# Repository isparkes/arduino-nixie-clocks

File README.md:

# ArdunixNix6 / ArdunixNix4 Version 2
Code for a 6-digit / 4-digit Nixie Clock based on Arduino with NeoPixel backlights

This is the main code for an Arduino based Nixie clock, intended for the following clocks:
- [ModularRev3](https://www.nixieclock.biz/StoreModular.html)
- [Classic Rev6](https://www.nixieclock.biz/StoreClassicRev6.html)

The firmware now also covers the older V1 clocks with RAGB LED backlights -
Classic Rev4 / Rev5, All-In-One IN-14 and the Arduino All-In-One shield - which
used to live in
[NixieClockFirmwareV1](https://bitbucket.org/isparkes/nixiefirmwarev1). Both
the 6 digit and the 4 digit firmware build for either generation; pick the
board with a single define at build time, see [Building](#building) below.

Version 356 converges the code bases for Classic Rev6 and Modular Rev 3.01. If you have a Modular Rev3, please see previous versions!

This repository now holds both the firmware and the KiCad hardware designs.
Firmware lives under `Software/` and is built with PlatformIO rather than the
Arduino IDE; the board designs live under `Hardware/`. The ESP8266 time
provider and the five hardware repositories were each developed separately
for a while and have been merged back in with their histories intact. Both
clock generations are covered, and which firmware a board takes follows
directly from its generation: **the Classic Rev6 and the Modular Rev 3 run
the V2 firmware; every other design here runs the V1 firmware.** See
[Which firmware runs on which board](#which-firmware-runs-on-which-board).

#### Features:
- Open source (CC BY-NC 4.0, see [LICENSE](LICENSE))
- Wifi Interface for an ESP8266 (included, see `Software/src/WifiTimeProviderESP8266/`)
- Real Time Clock interface for DS3231
- Digit fading with configurable fade length
- Digit scrollback with configurable scroll speed
- Configuration stored in EEPROM
- Low hardware component count (as much as possible done in code)
- Single button operation with software debounce
- Single K155ID1 for digit display (other versions use 2 or even 6!)
- Highly modular code
- RGB Back lighting
- Automatic linear dimming using light sensor

#### Building

The software is a [PlatformIO](https://platformio.org/) project. Install
PlatformIO Core (or the VSCode extension), then from the `Software/` directory:

```
pio run                                 # build everything
pio run -e nixie6digit                  # build the 6 digit clock firmware
pio run -e nixie4digit -t upload        # build and flash the 4 digit firmware
pio run -e wifitimeprovider -t upload   # build and flash the ESP8266 module
pio run -t clean                        # remove build products
pio device monitor                      # serial monitor
```

Pick the environment that matches your clock:

| Environment | Clock | Backlight | Source |
| --- | --- | --- | --- |
| `nixie6digit` | Classic Rev6, Modular Rev 3.01 | NeoPixel | `src/Firmware6Digit/` |
| `nixie6digitV1` | Classic Rev4 / Rev5, All-In-One IN-14, Arduino AIO shield | RAGB | `src/Firmware6Digit/` |
| `nixie6digitV1aio` | All-In-One Rev1 (mixed up tube wiring) | RAGB | `src/Firmware6Digit/` |
| `nixie4digit` | 4 digit V2 clocks | NeoPixel | `src/Firmware4Digit/` |
| `nixie4digitV1` | 4 digit V1 clocks | RAGB | `src/Firmware4Digit/` |
| `wifitimeprovider` | ESP8266 (ESP-01 / ESP-01S) time provider | - | `src/WifiTimeProviderESP8266/` |

Each source tree covers both clock generations. The environments that share a
tree differ only in the one define each passes - `FWV2`, `FWV1` or
`FWV1_AIO_REV1` - which is the only hardware switch in the code. Everything
else, the pin map, the backlight driver and whether the PIR and decimal point
menus exist, is derived from it. The variant is set in
`Software/platformio.ini` and nowhere else; see the "Hardware variant
selection" block at the top of each `main.cpp` for what the defines select.
There is no `FWV1_AIO_REV1` for the 4 digit tree, because the All-In-One Rev1
is a 6 digit clock.

The 4 and 6 digit trees are still separate. Their display layouts differ in
function signatures and menu structure, not just in pin maps, so folding them
together would need a refactor rather than another define.

The V1 builds report the same I2C protocol as the V2 builds, so they need a
current ESP8266 time provider. Its settings page will offer PIR and decimal
point options that a V1 clock does not have; they are simply ignored.

The clock firmwares assume a bare ATmega328P at 16 MHz / 5 V, as fitted to
the Classic Rev6 and Modular Rev 3.01 boards, flashed through the FTDI header.
If you are building on stock Arduino hardware, change `board` and
`upload_speed` in `Software/platformio.ini` - the alternatives for Uno and Nano
are listed in the comments there.

All libraries are pulled by PlatformIO rather than committed here, so the
first build of each target needs a network connection. Every version is
pinned in `Software/platformio.ini`; please rebuild and check the reported
flash use before floating any of them.

| Library | Version | Used by |
| --- | --- | --- |
| `paulstoffregen/Time` | 1.5 | all targets |
| `northernwidget/DS3231` | 1.1.2 | the clock firmwares |
| `adafruit/Adafruit NeoPixel` | 1.1.3 | the clock firmwares, except the V1 builds |
| `bblanchon/ArduinoJson` | 5.13.2 (git tag) | `wifitimeprovider` |
| `tzapu/WiFiManager` | 0.15.0 (git tag) | `wifitimeprovider` |
| `me-no-dev/ESPAsyncUDP` | master, pinned by commit | `wifitimeprovider` |

ArduinoJson 5 and WiFiManager 0.15.0 come from upstream git tags because the
PlatformIO registry no longer carries those versions.

The ESP8266 target is additionally pinned to Arduino core 2.7.4, because its
sketch header warns that the toolchain and library versions must match exactly
to compile cleanly. Its board settings reproduce the Arduino IDE board menu
recorded in that same header: Generic ESP8266 Module, 160 MHz CPU, 40 MHz QIO
flash, 1M flash with 64k SPIFFS, lwIP v2 low memory.

#### Which firmware runs on which board

The Classic Rev6 and the Modular Rev 3 are the V2 clocks: NeoPixel backlight,
PIR input and decimal points. Everything else in `Hardware/` is a V1 clock
with a single RAGB backlight on three PWM pins, no PIR and no decimal points.
Both generations are built from the same source, so the only thing that
changes is the environment you build:

| Design | Firmware | 6 digit environment | 4 digit environment |
| --- | --- | --- | --- |
| `Hardware/classic-rev-6/` | **V2** | `nixie6digit` | `nixie4digit` |
| `Hardware/modular-rev-3/` | **V2** | `nixie6digit` | `nixie4digit` |
| `Hardware/classic-rev-4/` | **V1** | `nixie6digitV1` | `nixie4digitV1` |
| `Hardware/classic-rev-5/` | **V1** | `nixie6digitV1` | `nixie4digitV1` |
| `Hardware/all-in-one/` | **V1** | `nixie6digitV1` | - |

Every design here drives six anodes. The Classic and Modular boards are
controller modules with the tubes on a connector, so the same board serves a
4 digit clock with four of them wired, which is what the 4 digit firmware
drives. The All-In-One carries its tubes on the board, so it is a 6 digit
clock only and has no 4 digit build.

The All-In-One boards here are Rev 004 and take the plain `FWV1` build. The
third V1 variant, `nixie6digitV1aio`, is for the earlier All-In-One Rev1,
whose tube wiring was mixed up and which needs its own digit mapping; that
board's design is not in this repository.

#### Known issues:
- `checkPIR()` in `Software/src/Firmware4Digit/main.cpp` writes `dpArray[4]`
  and `dpArray[5]`, but on the 4 digit clock that array only has four entries.
  The two writes run off the end of it. The indices were carried over from the
  6 digit code. This affects the `nixie4digit` build only - `nixie4digitV1` has
  no PIR and does not compile the function. Found during the V1 merge and left
  alone there so that the V2 build stayed unchanged; it still wants fixing.

#### Layout:
- `Hardware/all-in-one/`: KiCad designs for the V1 All-In-One clock, as the
  `all-in-one-in-14`, `all-in-one-in-8-2` and `all-in-one-z570m` boards, the
  flipped tube variants of the first two, and the `all-in-one-external`
  connector board
- `Hardware/classic-rev-4/`: KiCad design for the V1 Classic Rev4 clock, as
  the `ClassicRev4` module
- `Hardware/classic-rev-5/`: KiCad design for the V1 Classic Rev5 clock, as
  the `ClassicRev5` module
- `Hardware/classic-rev-6/`: KiCad design for the Classic Rev6 clock, as the
  `ClassicRev6` main board and the `ClassicRev6External` connector board
- `Hardware/modular-rev-3/`: KiCad design for the Modular Rev 3 clock, as the
  `ModularRev3` main board, the `ModularRev3External` connector board and a
  display board per tube type (IN-8, IN-8-2, IN-14, NL840, Z570, ZM1000)
- `Software/platformio.ini`: Build configuration for all firmware targets
- `Software/src/Firmware6Digit/`: Main code for every 6 Digit clock, V1 and V2
  alike, selected by one define per build environment (this was previously
  `FirmwareV2/`, and `main.cpp` before that `FirmwareV2.ino`)
- `Software/src/Firmware4Digit/`: Main code for every 4 Digit clock, V1 and V2
  alike, selected by one define per build environment (this was previously
  `FirmwareV2-4Digit/`, and `main.cpp` before that `FirmwareV2-4Digit.ino`)
- `Software/src/WifiTimeProviderESP8266/`: ESP8266 time provider module code
  (`main.cpp` was previously `WifiTimeProviderESP8266.ino`)
- `LICENSE`: The licence this work is released under

#### Imported history

The firmware, the ESP8266 time provider and the five hardware designs were
separate repositories, and each was merged in whole rather than copied, so
every commit that ever touched a file is still here. The fab tags came across
with their designs and do not collide: `Y48`, `Y49`, `Y53`, `Y100` and `Y103`
from the Modular Rev 3, `Y25` through `Y205` plus the `P*` and
`PCB_prototype_*` names from the All-In-One, `Rev4b` and `Rev4c` from the
Classic Rev4, alongside the firmware's own `v*` tags.

Each merge relocated the files into their directory under `Hardware/` in the
merge commit itself, leaving the imported commits at the paths they always
had. That keeps provenance exact, but it does mean `git log --follow` stops
at the merge, because history simplification follows the branch the file came
from, where the new path does not exist. To read a design's history before it
was merged, start from the merge's second parent and use the original path:

```
git log --oneline <merge>^2 -- ClassicRev4.kicad_sch
git log --oneline <merge>^2 -- ClassicRev5/ClassicRev5.kicad_sch
```

Three branches had no counterpart to merge into and are kept as-is under an
`imported/` prefix:

```
imported/wifi-time-provider/feature/web_interface
imported/all-in-one/AiO-ott-R4
imported/all-in-one/feature/drive-conditioning
```

Each predates its merge, so their files sit at the repository root rather
than under `Software/` or `Hardware/`. The `Y106-2132480A` tag is on the tip
of `AiO-ott-R4` rather than on master, so that branch is what keeps it
reachable.

#### Licence

This work is released under the
[Creative Commons Attribution-NonCommercial 4.0 International](https://creativecommons.org/licenses/by-nc/4.0/)
licence. You may share and adapt it for non-commercial purposes as long as you
give credit. The full terms are in [LICENSE](LICENSE).

The libraries listed above are fetched at build time, are not part of this
work, and carry their own licences.

**Instruction and User Manuals (including schematic) can be found at:** [Manuals](https://www.nixieclock.biz/Manuals.html)

You can buy this from: [https://www.nixieclock.biz/Store.html](https://www.nixieclock.biz/Store.html)

YouTube channel: [Ian's YouTube Channel](https://www.youtube.com/channel/UCiC34G8yl0mN2BK-LzPw0ew?view_as=subscriber)

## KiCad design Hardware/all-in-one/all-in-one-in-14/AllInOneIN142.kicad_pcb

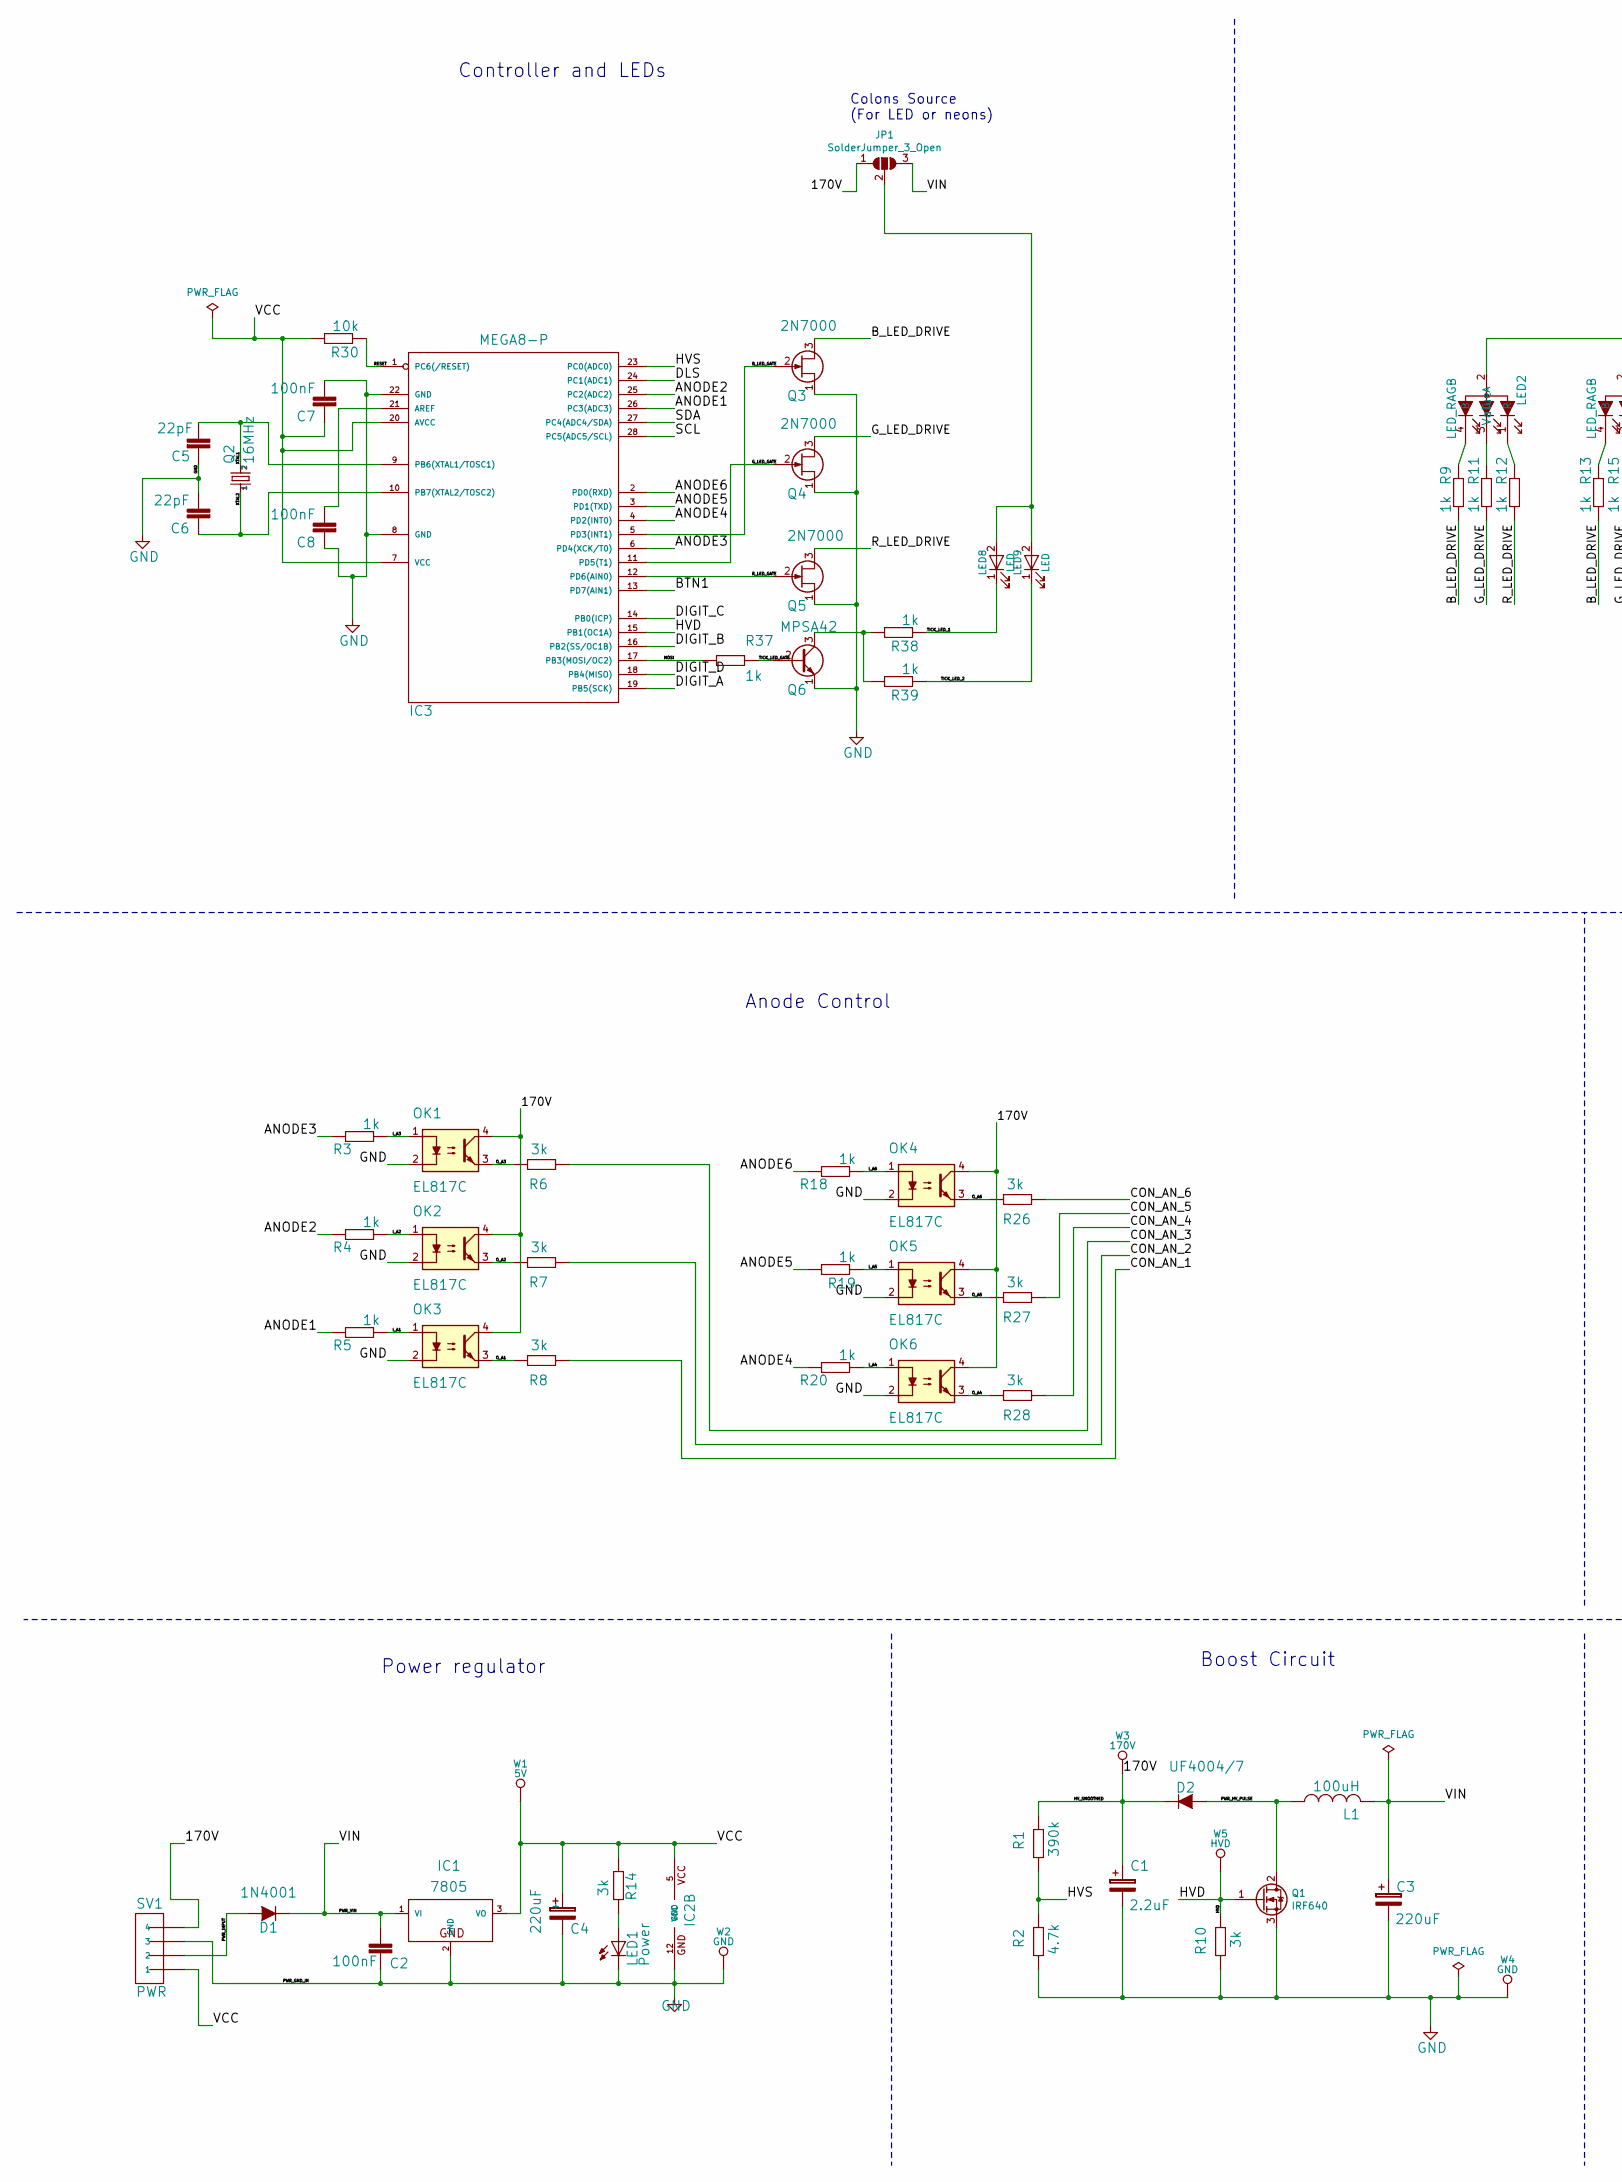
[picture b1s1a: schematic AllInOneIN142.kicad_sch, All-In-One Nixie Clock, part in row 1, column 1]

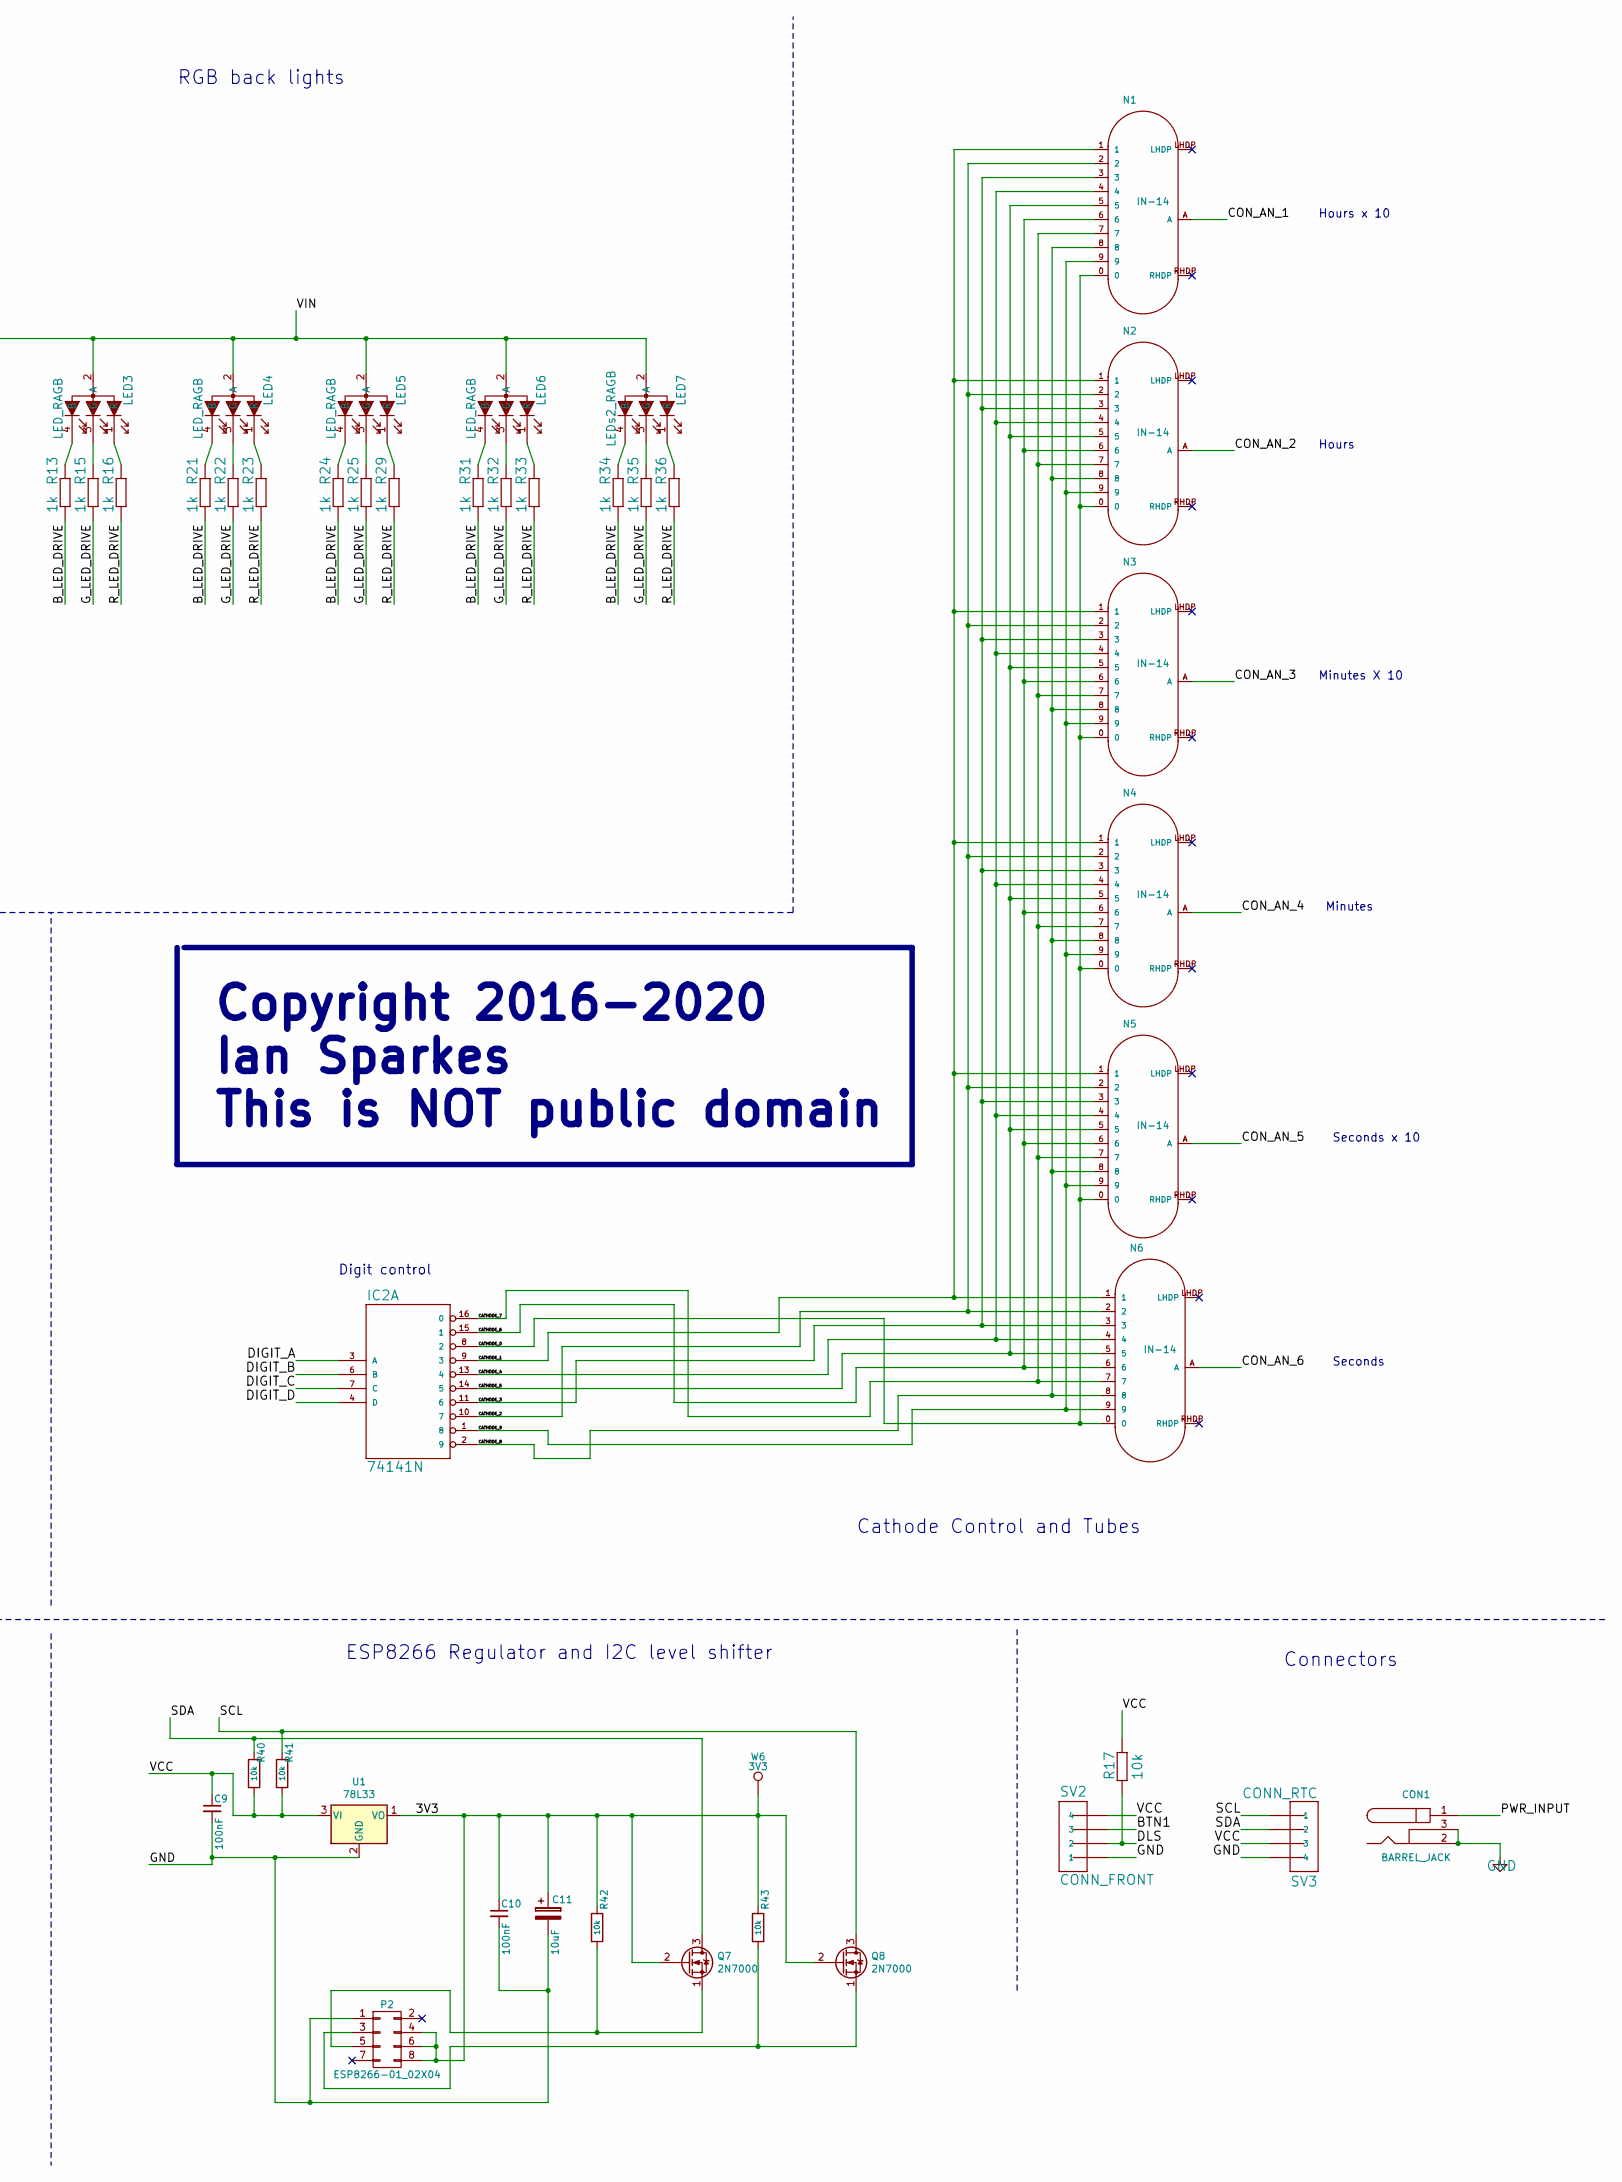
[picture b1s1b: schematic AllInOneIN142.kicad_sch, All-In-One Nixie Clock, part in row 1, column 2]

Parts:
C1: 2.2uF; C_Radial_D10_L11.2_P2.5_3.5
C2, C7, C8, C9, C10: 100nF; C025-024X044
C3, C4: 220uF; C_Radial_D6.3_L11.2_P2.5
C5, C6: 22pF; C025-024X044
C11: 10uF; C_Radial_D6.3_L11.2_P2.5
CON1: BARREL_JACK
D1: 1N4001; Diode_DO-41_1N4001
D2: UF4004/7; Diode_DO-41_1N4001
IC1: 7805; TRANSISTOR-POWER_TO220BV
IC2: 74141N; 74141_DIL16
IC3: MEGA8-P; 328P_DIL28
JP1: SolderJumper_3_Open; SOLDER-JUMPER_2-WAY
L1: 100uH; Inductor-100mH
LED1: Power; LED_3MM
LED2, LED3, LED4, LED5, LED6: LED_RAGB; LED5_RGB_CA_Offset
LED7: LEDs2_RAGB; LED5_RGB_CA_Offset
LED8, LED9: LED; LED-5MM-Centred
N1, N2, N3, N4, N5, N6: IN-14
OK1, OK2, OK3, OK4, OK5, OK6: EL817C; optocoupler-DIL04
P2: ESP8266-01_02X04; ESP8266_2x04
Q1: IRF640; TO-220-3_H
Q2: 16MHz; Crystal_HC49-U_Vertical
Q3, Q4, Q5: 2N7000; TO-92_inline_2N7000
Q6: MPSA42; TO-92_inline_MPSA42
Q7, Q8: 2N7000; TO-92_2N7000_inline
R1: 390k; RCL_0207/2V
R2: 4.7k; RCL_0207/2V
R3, R4, R5, R9, R11, R12, R13, R15, R16, R18, R19, R20, R21, R22, R23, R24, R25, R29, R31, R32, R33, R34, R35, R36, R37, R38, R39: 1k; RCL_0207/2V
R6, R7, R8, R10, R14, R26, R27, R28: 3k; RCL_0207/2V
R17, R30: 10k; RCL_0207/2V
R40, R41, R42, R43: 10k; R-0207_2V
SV1: PWR; Header_MA04-1
SV2: CONN_FRONT; Header_MA04-1
SV3: CONN_RTC; Header_MA04-1
U1: 78L33; TO-92_2N7000_inline
W1: 5V; TESTPAD_P1-13
W2, W4: GND; TESTPAD_P1-13
W3: 170V; TESTPAD_P1-13
W5: HVD; TESTPAD_P1-13
W6: 3V3; TESTPAD_P1-13

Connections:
/3V3: C10.1, C11.1, P2.4 (CH_EN), P2.6 (RST), P2.8 (VCC), Q7.2 (G), Q8.2 (G), R42.1, R43.1, U1.1 (VO), W6.1
/170V: C1.1, D2.1 (K), JP1.1 (A), OK1.4, OK2.4, OK3.4, OK4.4, OK5.4, OK6.4, R1.2, SV1.4, W3.1
/ANODE1: IC3.26 (PC3(ADC3)), R5.2
/ANODE2: IC3.25 (PC2(ADC2)), R4.2
/ANODE3: IC3.6 (PD4(XCK/T0)), R3.2
/ANODE4: IC3.4 (PD2(INT0)), R20.2
/ANODE5: IC3.3 (PD1(TXD)), R19.2
/ANODE6: IC3.2 (PD0(RXD)), R18.2
/BTN1: IC3.13 (PD7(AIN1)), SV2.3
/B_LED_DRIVE: Q3.3 (D), R9.1, R13.1, R21.1, R24.1, R31.1, R34.1
/B_LED_GATE: IC3.5 (PD3(INT1)), Q3.2 (G)
/CATHODE_0: IC2.8 (2), N1.0, N2.0, N3.0, N4.0, N5.0, N6.0
/CATHODE_1: IC2.9 (3), N1.1, N2.1, N3.1, N4.1, N5.1, N6.1
/CATHODE_2: IC2.10 (7), N1.2, N2.2, N3.2, N4.2, N5.2, N6.2
/CATHODE_3: IC2.11 (6), N1.3, N2.3, N3.3, N4.3, N5.3, N6.3
/CATHODE_4: IC2.13 (4), N1.4, N2.4, N3.4, N4.4, N5.4, N6.4
/CATHODE_5: IC2.14 (5), N1.5, N2.5, N3.5, N4.5, N5.5, N6.5
/CATHODE_6: IC2.15 (1), N1.6, N2.6, N3.6, N4.6, N5.6, N6.6
/CATHODE_7: IC2.16 (0), N1.7, N2.7, N3.7, N4.7, N5.7, N6.7
/CATHODE_8: IC2.2 (9), N1.8, N2.8, N3.8, N4.8, N5.8, N6.8
/CATHODE_9: IC2.1 (8), N1.9, N2.9, N3.9, N4.9, N5.9, N6.9
/CON_AN_1: N1.A, R8.1
/CON_AN_2: N2.A, R7.1
/CON_AN_3: N3.A, R6.1
/CON_AN_4: N4.A, R28.1
/CON_AN_5: N5.A, R27.1
/CON_AN_6: N6.A, R26.1
/DIGIT_A: IC2.3 (A), IC3.19 (PB5(SCK))
/DIGIT_B: IC2.6 (B), IC3.16 (PB2(SS/OC1B))
/DIGIT_C: IC2.7 (C), IC3.14 (PB0(ICP))
/DIGIT_D: IC2.4 (D), IC3.18 (PB4(MISO))
/DLS: IC3.24 (PC1(ADC1)), R17.1, SV2.2
/G_LED_DRIVE: Q4.3 (D), R11.1, R15.1, R22.1, R25.1, R32.1, R35.1
/G_LED_GATE: IC3.11 (PD5(T1)), Q4.2 (G)
/HVD: IC3.15 (PB1(OC1A)), Q1.1 (G), R10.2, W5.1
/HVS: IC3.23 (PC0(ADC0)), R1.1, R2.2
/I_A1: OK3.1, R5.1
/I_A2: OK2.1, R4.1
/I_A3: OK1.1, R3.1
/I_A4: OK6.1, R20.1
/I_A5: OK5.1, R19.1
/I_A6: OK4.1, R18.1
/MOSI: IC3.17 (PB3(MOSI/OC2)), R37.1
/O_A1: OK3.3, R8.2
/O_A2: OK2.3, R7.2
/O_A3: OK1.3, R6.2
/O_A4: OK6.3, R28.2
/O_A5: OK5.3, R27.2
/O_A6: OK4.3, R26.2
/PWR_HV_PULSE: D2.2 (A), L1.1, Q1.2 (D)
/PWR_INPUT: CON1.1, D1.2 (A), SV1.2
/PWR_VIN: C2.2, C3.1, D1.1 (K), IC1.1 (VI), JP1.3 (B), L1.2, LED2.2 (A), LED3.2 (A), LED4.2 (A), LED5.2 (A), LED6.2 (A), LED7.2 (A)
/RESET: IC3.1 (PC6(/RESET)), R30.1
/R_LED_DRIVE: Q5.3 (D), R12.1, R16.1, R23.1, R29.1, R33.1, R36.1
/R_LED_GATE: IC3.12 (PD6(AIN0)), Q5.2 (G)
/SCL: IC3.28 (PC5(ADC5/SCL)), Q8.3 (D), R41.1, SV3.1
/SDA: IC3.27 (PC4(ADC4/SDA)), Q7.3 (D), R40.1, SV3.2
/TICK_LED_1: LED8.1 (K), R38.1
/TICK_LED_2: LED9.1 (K), R39.1
/TICK_LED_GATE: Q6.2 (B), R37.2
/VCC: C4.1, C7.1, C9.1, IC1.3 (VO), IC2.5 (VCC), IC3.7 (VCC), IC3.20 (AVCC), R14.1, R17.2, R30.2, R40.2, R41.2, SV1.1, SV2.4, SV3.3, U1.3 (VI), W1.1
/XTAL1: C5.2, IC3.9 (PB6(XTAL1/TOSC1)), Q2.2
/XTAL2: C6.1, IC3.10 (PB7(XTAL2/TOSC2)), Q2.1
GND: C1.2, C2.1, C3.2, C4.2, C5.1, C6.2, C7.2, C8.1, C9.2, C10.2, C11.2, CON1.2, CON1.3, IC1.2 (GND), IC2.12 (GND), IC3.8 (GND), IC3.22 (GND), LED1.K (C), OK1.2, OK2.2, OK3.2, OK4.2, OK5.2, OK6.2, P2.1 (GND), Q1.3 (S), Q3.1 (S), Q4.1 (S), Q5.1 (S), Q6.1 (E), R2.1, R10.1, SV1.3, SV2.1, SV3.4, U1.2 (GND), W2.1, W4.1; also elsewhere on the board
unnamed: C8.2, IC3.21 (AREF)
unnamed: JP1.2 (C), LED8.2 (A), LED9.2 (A)
unnamed: LED1.A, R14.2
unnamed: LED2.1 (R), R12.2
unnamed: LED2.3 (G), R11.2
unnamed: LED2.4 (B), R9.2
unnamed: LED3.1 (R), R16.2
unnamed: LED3.3 (G), R15.2
unnamed: LED3.4 (B), R13.2
unnamed: LED4.1 (R), R23.2
unnamed: LED4.3 (G), R22.2
unnamed: LED4.4 (B), R21.2
unnamed: LED5.1 (R), R29.2
unnamed: LED5.3 (G), R25.2
unnamed: LED5.4 (B), R24.2
unnamed: LED6.1 (R), R33.2
unnamed: LED6.3 (G), R32.2
unnamed: LED6.4 (B), R31.2
unnamed: LED7.1 (R), R36.2
unnamed: LED7.3 (G), R35.2
unnamed: LED7.4 (B), R34.2
unnamed: P2.3 (GPIO2), Q8.1 (S), R43.2
unnamed: P2.5 (GPIO0), Q7.1 (S), R42.2
unnamed: Q6.3 (C), R38.2, R39.2

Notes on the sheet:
Seconds
Hours
Digit control
Copyright 2016-2020 Ian Sparkes This is NOT public domain
Cathode Control and Tubes
Power regulator
Minutes
Colons Source (For LED or neons)
Controller and LEDs
Minutes X 10
Connectors
Anode Control
Hours x 10
ESP8266 Regulator and I2C level shifter
Boost Circuit
RGB back lights
Seconds x 10

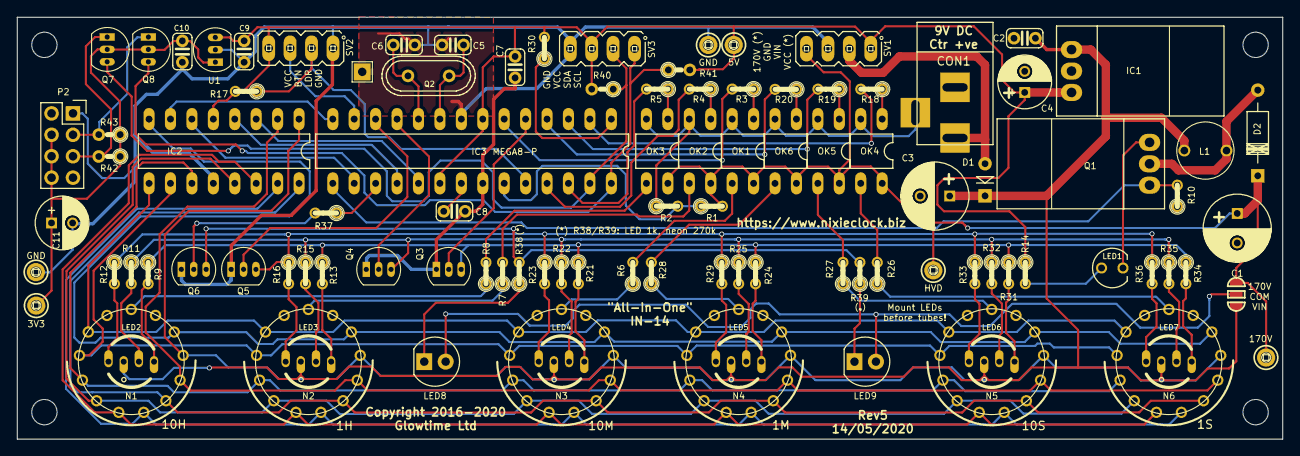
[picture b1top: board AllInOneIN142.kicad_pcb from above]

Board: 2 copper layers, 150.0 x 50.0 mm, 107 parts (0 on the bottom side), 88 nets.

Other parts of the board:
GND Can: TestPoint_THTPad_2.0x2.0mm_Drill1.0mm
MH1, MH2, MH3, MH4: MountingHole_3mm

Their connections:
GND: GND Can.1; also elsewhere on the board

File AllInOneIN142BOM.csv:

"Id";"Designator";"Package";"Quantity";"Designation";"Supplier and ref";
1;"W2,W2";"Measurement_Point_Round-TH_Big";2;"GND";;;
2;"C5,C6";"rcl-C050-024X044";2;"22pF";;;
3;"LED9,LED8";"LED-5MM-Centred";2;"LED";;;
4;"C1";"C_Radial_D8_L11.5_P3.5";1;"2.2uF";;;
5;"C3,C4";"C_Radial_D8_L11.5_P3.5";2;"220uF";;;
6;"W1";"Measurement_Point_Round-TH_Big";1;"VCC";;;
7;"W3";"Measurement_Point_Round-TH_Big";1;"170V";;;
8;"LED2,LED7,LED6,LED5,LED4,LED3";"LED5_RGB_CA";6;"LED_RAGB";;;
9;"Q2";"Crystal_HC49-U_Vertical";1;"16MHz";;;
10;"D2";"Diode_DO-41_1N4001";1;"UF4004/7";;;
11;"D1";"Diode_DO-41_1N4001";1;"1N4001";;;
12;"REF**,REF**,REF**,REF**";"MountingHole_3mm";4;"MountingHole_3mm";;;
13;"IC2";"74141_DIL16";1;"74141N";;;
14;"R2";"R-0207_2V";1;"4.7k";;;
15;"R1";"R-0207_2V";1;"390k";;;
16;"R14,R7,R8,R28,R27,R26,R6,R10";"R-0207_2V";8;"3k";;;
17;"R13,R12,R9,R11,R3,R19,R18,R23,R39,R20,R21,R22,R24,R25,R29,R31,R32,R33,R34,R35,R36,R37,R38,R4,R5,R15,R16";"R-0207_2V";27;"1k";;;
18;"R30,R17";"R-0207_2V";2;"10k";;;
19;"IC3";"328P_DIL28";1;"MEGA8-P";;;
20;"OK1,OK2,OK3,OK4,OK5,OK6";"optocoupler-DIL04";6;"EL817C";;;
21;"SV2";"Header_MA04-1";1;"CONN_FRONT";;;
22;"SV3";"Header_MA04-1";1;"CONN_RTC";;;
23;"SV1";"Header_MA04-1";1;"PWR";;;
24;"Q3,Q4,Q5,Q6";"2N7000_TO92";4;"2N7000";;;
25;"C7,C2,C8";"rcl-C050-024X044";3;"100nF";;;
26;"P1";"Header_MA03-1";1;"CONN_01X03";;;
27;"LED1";"LED_3MM";1;"Power";;;
28;"L1";"Inductor-100mH";1;"100uH";;;
29;"IC1";"7805_TO220V";1;"7805";;;
30;"Q1";"TRANSISTOR-POWER_TO220BV";1;"IRF740";;;
31;"N2,N5,N4,N3,N6,N1";"IN-14";6;"IN-14";;;

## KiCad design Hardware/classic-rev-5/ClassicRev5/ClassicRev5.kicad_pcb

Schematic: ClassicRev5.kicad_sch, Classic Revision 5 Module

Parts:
C1: 2.2uF; C_Radial_D10_L11.2_P2.5_3.5_5
C2, C3, C7, C8, C10: 100nF; C025-024X044
C4, C9: 220uF; C_Radial_D6.3_L11.2_P2.5
C5, C6: 22pF; C025-024X044
C11: 10uF; C_Radial_D6.3_L11.2_P2.5
CON1: BARREL_JACK
D1: UF4007; Diode_DO-41_1N4001
D2: UF4007; Diode_DO-41_SOD81_Vertical_AnodeUp
D3: 1N5819; Diode_DO-41_SOD81_Vertical_AnodeUp
H1, H2, H3, H4: MountingHole; MountingHole_3mm_M3
IC1: LM2596T-5; TO220-5A
IC2: MEGA8-P; 328P_DIL28
IC3: 74141N; 74141_DIL16
L1: 100uH; Inductor-100mH
L2: 33uH; Inductor-33mH-TH
LED1: Power; LED_3MM
OK1, OK2, OK3, OK4, OK5, OK6: EL817C; optocoupler-DIL04
P1: ESP8266-01_02X04; ESP8266_2x04
Q1: IRF640; TRANSISTOR-POWER_TO220BV
Q2: 16MHz; Crystal_HC49-U_Vertical
Q3, Q4, Q5: 2N7000; 2N7000_TO92
Q6: MPSA42; 2N7000_TO92
Q7, Q8: 2N7000; TO-92_2N7000_inline
R1, R2, R3, R12, R13, R14, R19, R20, R21, R22, R23: 1k; R-0207_2V
R4, R5, R6, R15, R16, R17: 3k; R-0207_2V
R7, R8: 2.7k; R-0207_2V
R9: 390k; R-0207_2V
R10: 4.7k; R-0207_2V
R11, R18, R24, R25, R26, R27: 10k; R-0207_2V
SV1: PWR; Header_MA04-1
SV2: CONN_FRONT; Header_MA04-1
SV3: CONN_01X06; Header_MA06-1
SV4: CONN_RTC; Header_MA04-1
SV5: CONN_01X10; Header_MA10-1
SV6: CONN_LED; Header_MA04-1
SV7: CONN_ISCP; Header_MA03-1
TP1: HV; TESTPAD_P1-13
TP2: GND; TESTPAD_P1-13
TP3: VCC; TESTPAD_P1-13
TP4: HVD; TESTPAD_P1-13
TP5: VIN; TESTPAD_P1-13
TP6: 3V3; TESTPAD_P1-13
U1: L78L05_TO92; TO-92_2N7000_inline

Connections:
/3V3: C10.1, C11.1, P1.4 (CH_EN), P1.6 (RST), P1.8 (VCC), Q7.2 (G), Q8.2 (G), R26.1, R27.1, TP6.1, U1.1 (VO)
/170V: C1.1, D2.1 (K), OK1.4, OK2.4, OK3.4, OK4.4, OK5.4, OK6.4, R9.2, SV1.4, TP1.1
/ANODE1: IC2.2 (PD0(RXD)), R3.2
/ANODE2: IC2.3 (PD1(TXD)), R2.2
/ANODE3: IC2.4 (PD2(INT0)), R1.2
/ANODE4: IC2.6 (PD4(XCK/T0)), R14.2
/ANODE5: IC2.25 (PC2(ADC2)), R13.2
/ANODE6: IC2.26 (PC3(ADC3)), R12.2
/AREF: C8.2, IC2.21 (AREF)
/BTN1: IC2.13 (PD7(AIN1)), SV2.3
/B_LED: R20.1, SV6.3
/CATHODE_0: IC3.8 (2), SV5.1
/CATHODE_1: IC3.9 (3), SV5.2
/CATHODE_2: IC3.10 (7), SV5.3
/CATHODE_3: IC3.11 (6), SV5.4
/CATHODE_4: IC3.13 (4), SV5.5
/CATHODE_5: IC3.14 (5), SV5.6
/CATHODE_6: IC3.15 (1), SV5.7
/CATHODE_7: IC3.16 (0), SV5.8
/CATHODE_8: IC3.2 (9), SV5.9
/CATHODE_9: IC3.1 (8), SV5.10
/DIGIT_A: IC2.19 (PB5(SCK)), IC3.3 (A), SV7.3
/DIGIT_B: IC2.16 (PB2(SS/OC1B)), IC3.6 (B)
/DIGIT_C: IC2.14 (PB0(ICP)), IC3.7 (C)
/DIGIT_D: IC2.18 (PB4(MISO)), IC3.4 (D), SV7.1
/DLS: IC2.24 (PC1(ADC1)), R11.1, SV2.2
/DRAIN: D2.2 (A), L1.1, Q1.D
/G_LED: R21.1, SV6.2
/HVD: IC2.15 (PB1(OC1A)), Q1.G, R7.2, TP4.1
/HVS: IC2.23 (PC0(ADC0)), R9.1, R10.2
/MOSI: IC2.17 (PB3(MOSI/OC2)), R23.1, SV7.4
/N$31: IC2.5 (PD3(INT1)), Q3.2 (G)
/N$32: IC2.12 (PD6(AIN0)), Q5.2 (G)
/N$35: IC2.11 (PD5(T1)), Q4.2 (G)
/RAW_VIN: CON1.1, D1.2 (A), SV1.2
/RESET: IC2.1 (PC6(/RESET)), R18.1, SV7.5
/R_LED: R22.1, SV6.1
/SCL: IC2.28 (PC5(ADC5/SCL)), Q8.3 (D), R25.1, SV4.1
/SDA: IC2.27 (PC4(ADC4/SDA)), Q7.3 (D), R24.1, SV4.2
/TICK_LED: R19.1, SV6.4
/VCC: C3.1, C7.1, C9.1, IC1.4 (FB), IC2.7 (VCC), IC2.20 (AVCC), IC3.5 (VCC), L2.2, R8.1, R11.2, R18.2, R24.2, R25.2, SV1.1, SV2.4, SV4.3, SV7.2, TP3.1, U1.3 (VI)
/VIN: C2.2, C4.1, D1.1 (K), IC1.1 (VIN), L1.2, TP5.1
/XTAL1: C5.2, IC2.9 (PB6(XTAL1/TOSC1)), Q2.2
/XTAL2: C6.1, IC2.10 (PB7(XTAL2/TOSC2)), Q2.1
GND: C1.2, C2.1, C3.2, C4.2, C5.1, C6.2, C7.2, C8.1, C9.2, C10.2, C11.2, CON1.2, CON1.3, D3.2 (A), IC1.3 (GND), IC1.5 (~ON/OFF), IC2.8 (GND), IC2.22 (GND), IC3.12 (GND), LED1.K (C), OK1.2, OK2.2, OK3.2, OK4.2, OK5.2, OK6.2, P1.1 (GND), Q1.S, Q3.3 (S), Q4.3 (S), Q5.3 (S), Q6.3 (E), R7.1, R10.1, SV1.3, SV2.1, SV4.4, SV7.6, TP2.1, U1.2 (GND)
unnamed: D3.1 (K), IC1.2 (OUT), L2.1
unnamed: LED1.A, R8.2
unnamed: OK1.1, R3.1
unnamed: OK1.3, R6.2
unnamed: OK2.1, R2.1
unnamed: OK2.3, R5.2
unnamed: OK3.1, R1.1
unnamed: OK3.3, R4.2
unnamed: OK4.1, R14.1
unnamed: OK4.3, R17.2
unnamed: OK5.1, R13.1
unnamed: OK5.3, R16.2
unnamed: OK6.1, R12.1
unnamed: OK6.3, R15.2
unnamed: P1.3 (GPIO2), Q8.1 (S), R27.2
unnamed: P1.5 (GPIO0), Q7.1 (S), R26.2
unnamed: Q3.1 (D), R20.2
unnamed: Q4.1 (D), R21.2
unnamed: Q5.1 (D), R22.2
unnamed: Q6.1 (C), R19.2
unnamed: Q6.2 (B), R23.2
unnamed: R4.1, SV3.4
unnamed: R5.1, SV3.5
unnamed: R6.1, SV3.6
unnamed: R15.1, SV3.1
unnamed: R16.1, SV3.2
unnamed: R17.1, SV3.3

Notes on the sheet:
Cathode control
Anode Control
Power regulator
Connections
ESP8266 Regulator and I2C level shifter
Connectors
Boost Circuit
Controller

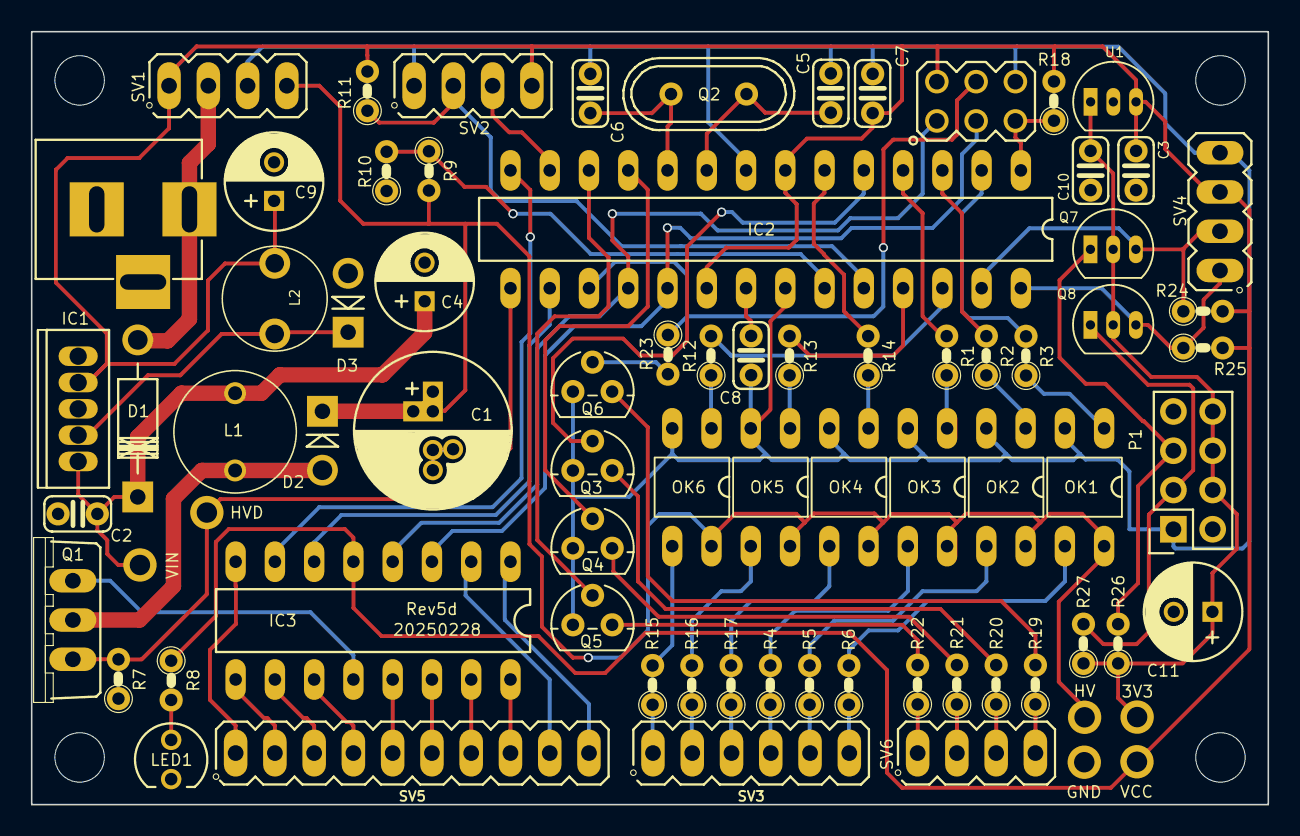
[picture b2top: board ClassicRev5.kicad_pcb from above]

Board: 2 copper layers, 80.0 x 50.0 mm, 81 parts (0 on the bottom side), 72 nets.

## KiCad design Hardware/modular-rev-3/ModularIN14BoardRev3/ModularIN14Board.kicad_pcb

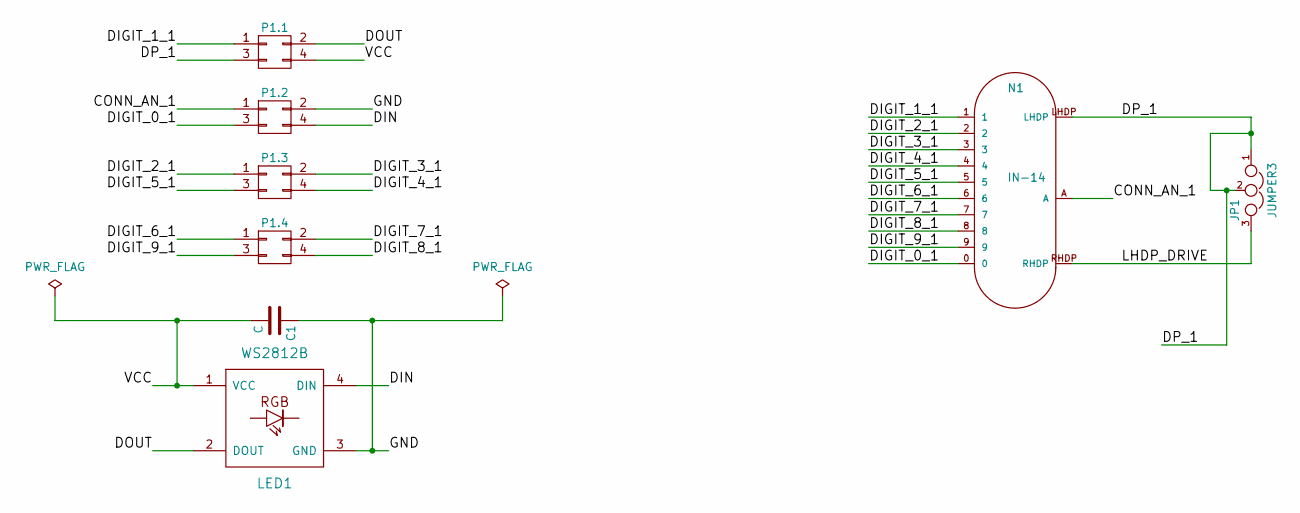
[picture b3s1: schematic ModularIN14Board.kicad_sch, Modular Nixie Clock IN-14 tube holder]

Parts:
C1: C; C_1206_HandSoldering
JP1: JUMPER3; SOLDER-JUMPER_2-WAY
LED1: WS2812B; WS2812B_Bottom_Thru
N1: IN-14
P1.1, P1.2, P1.3, P1.4: CONN_02X02; Header_MA02-2_RearMount

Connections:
/CONN_AN_1: N1.A, P1.2.1
/DIGIT_0_1: N1.0, P1.2.3
/DIGIT_1_1: N1.1, P1.1.1
/DIGIT_2_1: N1.2, P1.3.1
/DIGIT_3_1: N1.3, P1.3.2
/DIGIT_4_1: N1.4, P1.3.4
/DIGIT_5_1: N1.5, P1.3.3
/DIGIT_6_1: N1.6, P1.4.1
/DIGIT_7_1: N1.7, P1.4.2
/DIGIT_8_1: N1.8, P1.4.4
/DIGIT_9_1: N1.9, P1.4.3
/DIN: LED1.4 (DIN), P1.2.4
/DOUT: LED1.2 (DOUT), P1.1.2
/DP_1: JP1.1, JP1.2, N1.LHDP, P1.1.3
/GND: C1.1, LED1.3 (GND), P1.2.2
/LHDP_DRIVE: JP1.3, N1.RHDP
/VCC: C1.2, LED1.1 (VCC), P1.1.4

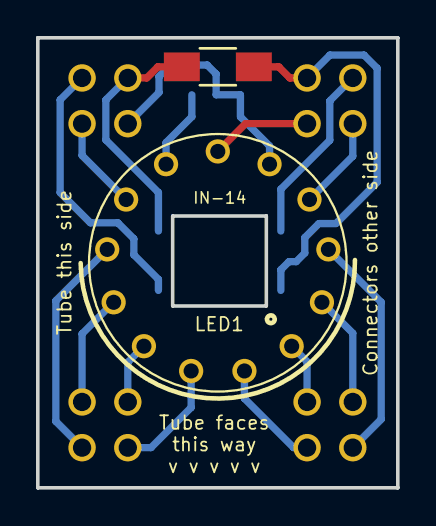
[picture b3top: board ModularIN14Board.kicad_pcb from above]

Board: 2 copper layers, 20.0 x 25.0 mm, 8 parts (1 on the bottom side), 17 nets.

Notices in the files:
Hardware/all-in-one/all-in-one-in-14-flip/AllInOneIN142.kicad_sch:
Copyright 2016-2019
Hardware/modular-rev-3/ModularRev3/ModularRev3.kicad_pcb:
Copyright 2017-2020 Ian Sparkes
